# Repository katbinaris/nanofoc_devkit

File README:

# NanoFOC DevKit++
<sub>Revision C.03.23</sub>

## What is it?

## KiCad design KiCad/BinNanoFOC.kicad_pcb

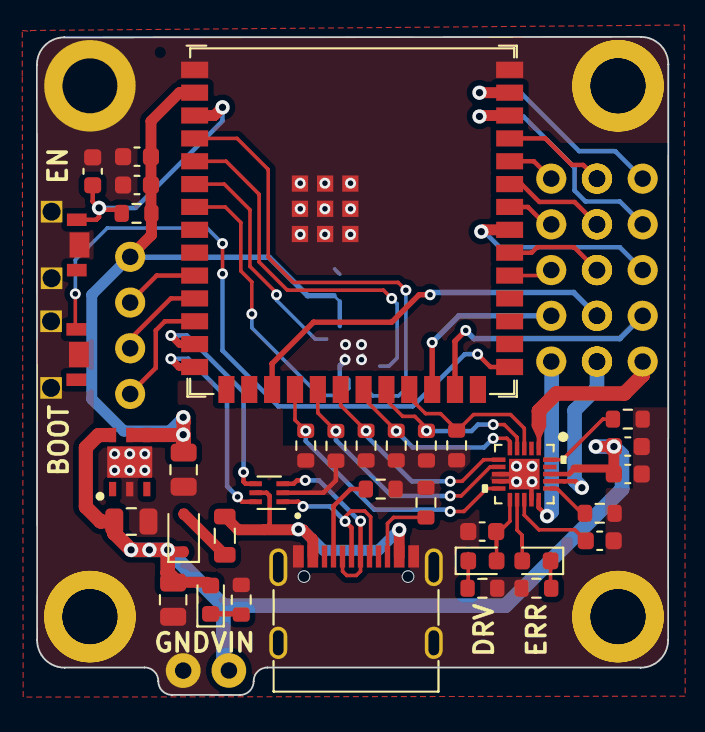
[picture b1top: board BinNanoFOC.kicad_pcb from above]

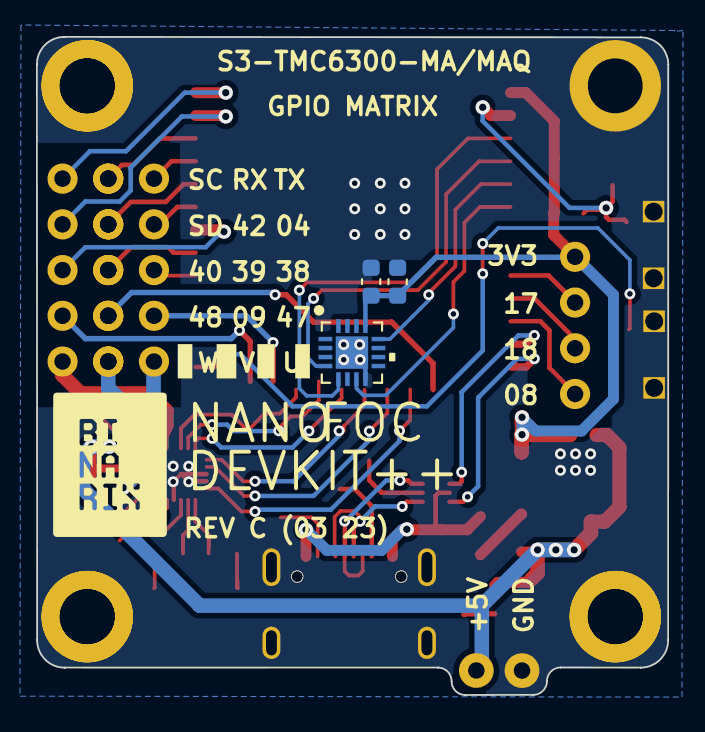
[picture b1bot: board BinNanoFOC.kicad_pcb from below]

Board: 2 copper layers, 35.1 x 36.6 mm, 39 parts (3 on the bottom side), 30 nets.

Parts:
C1, C2, C4, C8, C12: 100nF; C_0603_1608Metric
C3: 10uF; C_0603_1608Metric
C5, C6: 4.7uF; C_0805_2012Metric
C7, C13: 1uF; C_0603_1608Metric
C9: 22uF; C_0805_2012Metric
C11: 22uF; C_0603_1608Metric
D3: NUF2042XV6T1G; SOT-563
D4: D; D_SOD-323
D5: LED; LED_0603_1608Metric
DIAG: ERROR; LED_0603_1608Metric
DRV: DRIVER; LED_0603_1608Metric
IC1: ST1L05CPU33R; SON95P300X300X100-7N-D
L1: 100Mhz 40Ohm 1.5A; L_0805_2012Metric
P1: USB_C_Plug; USB_C_Receptacle_G-Switch_GT-USB-7010ASV
R1, R2, R3, R4, R5, R6: 100K; R_0603_1608Metric
R7, R8: 300R; R_0603_1608Metric
R9, R10: 300M; R_0603_1608Metric
R13, R13#2: 5.1K; R_0603_1608Metric
R14: 350R; R_0603_1608Metric
R15: 10K; R_0603_1608Metric
SW1, SW2: SW_MEC_5E; SKTDLDE010
U1: ESP32-S3-WROOM-1; ESP32-S3-WROOM-1U
U2: TMC6300-LA
U3: MAQ430GQE-AEC1-P

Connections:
+3.3V: C6.2, C7.1, C8.1, C11.1, C12.1, IC1.4 (VO), IC1.5 (V_O_SENSE), R15.1, U1.2 (3V3), U3.13 (VDD)
BOOT: SW1.3 (K), U1.27 (GPIO0/BOOT)
BRUV: R9.1, U2.16 (BRUV)
BRW: R10.1, U2.20 (BRW)
EN: C13.1, R15.2, SW2.3 (K), U1.3 (EN)
GND: C1.2, C2.2, C3.2, C4.2, C5.2, C6.1, C7.2, C8.2, C9.2, C11.2, C12.2, C13.2, D3.2 (GND), IC1.2 (GND), IC1.7 (EP), P1.A1 (GND), P1.A12 (GND), P1.B1 (GND), P1.B12 (GND), P1.S1 (SHIELD), R1.2, R2.2, R3.2, R4.2, R5.2, R6.2, R7.2, R8.2, R9.2, R10.2, R13.1, R13#2.1, R14.2, SW1.1, SW1.2, SW2.1, SW2.2, U1.1 (GND), U1.40 (GND), U1.41 (GND), U2.8 (GND), U2.9 (GND), U2.14 (GND), U2.21 (EPAD), U3.8 (GND), U3.17 (PAD)
IN_UH: R6.1, U1.23 (GPIO21), U2.3 (UH)
IN_UL: R3.1, U1.20 (GPIO12/TOUCH12/ADC2_CH1/FSPICLK/FSPIIO6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), U2.6 (UL)
IN_VH: R5.1, U1.22 (GPIO14/TOUCH14/ADC2_CH3/FSPIWP/FSPIDQS/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), U2.4 (VH)
IN_VL: R1.1, U1.18 (GPIO10/TOUCH10/ADC1_CH9/FSPICS0/FSPIIO4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), U2.10 (VL)
IN_WH: R4.1, U1.21 (GPIO13/TOUCH13/ADC2_CH2/FSPIQ/FSPIIO7/S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), U2.5 (WH)
IN_WL: R2.1, U1.19 (GPIO11/TOUCH11/ADC2_CH0/FSPID/FSPIIO5/S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), U2.7 (WL)
MAQ_CS: U1.4 (GPIO4/TOUCH4/ADC1_CH3), U3.5 (CS)
MAQ_MISO: U1.7 (GPIO7/TOUCH7/ADC1_CH6), U3.7 (MISO)
MAQ_MOSI: U1.5 (GPIO5/TOUCH5/ADC1_CH4), U3.4 (MOSI)
MAQ_SCLK: U1.6 (GPIO6/TOUCH6/ADC1_CH5), U3.12 (SCLK)
MCU_D+: D3.6 (D1(0)), U1.14 (GPIO20/U1CTS/ADC2_CH9/CLK_OUT1/USB_D+)
MCU_D-: D3.4 (D2(0)), U1.13 (GPIO19/U1RTS/ADC2_CH8/CLK_OUT2/USB_D-)
unnamed: C1.1, DRV.2 (A), U2.11 (VIO/NSTDBY)
unnamed: DRV.1 (K), R7.1
unnamed: DIAG.2 (A), U2.12 (DIAG)
unnamed: DIAG.1 (K), R8.1
unnamed: D4.2 (A), L1.2
unnamed: D5.1 (K), R14.1
unnamed: P1.A5 (CC), P1.B5 (VCONN), R13.2, R13#2.2
unnamed: C2.1, U2.13 (1-8VOUT)
USB_D+: D3.1 (D1(I)), P1.A6 (D+), P1.B6
USB_D-: D3.3 (D2(I)), P1.A7 (D-), P1.B7
VBUS: D3.5 (VBUS), L1.1, P1.A4 (VBUS), P1.A9 (VBUS), P1.B4 (VBUS), P1.B9 (VBUS)
VS: C3.1, C4.1, C5.1, C9.1, D4.1 (K), D5.2 (A), IC1.6 (VI), U2.18 (VS)

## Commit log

2023-03-28 Rename README to README.md
2023-04-28 Init
    Updated Rev.C.3.23, PCB, Schematic & Project.
2023-04-28 KiCad Update
2023-04-28 Assets Initial Commit
2023-04-28 Redundant Images Clean Up
2023-05-10 Haptic Textures Example Init
2023-05-11 Update platformio.ini
    Added lib_deps SimpleFOC
2023-05-13 add microdelay, add disclaimer
2023-05-15 Update safe PID values
2023-05-16 Advanced Example Init
    Advanced Example of Haptic Textures based on SmartKnob project repository by Scot Bezek
2023-05-30 Updated BOM + Link to SmartKnob
